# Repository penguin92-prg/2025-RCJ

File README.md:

# 2025-RCJ

## 👥Member

#### penguin92-prg [(bio)](https://github.com/penguin92-prg)
#### maguronoosushi0807 [(bio)](https://github.com/maguronoosushi0807)

## 🔗Links

- [penguin92-prg's blog](https://note.com/nearfactory)

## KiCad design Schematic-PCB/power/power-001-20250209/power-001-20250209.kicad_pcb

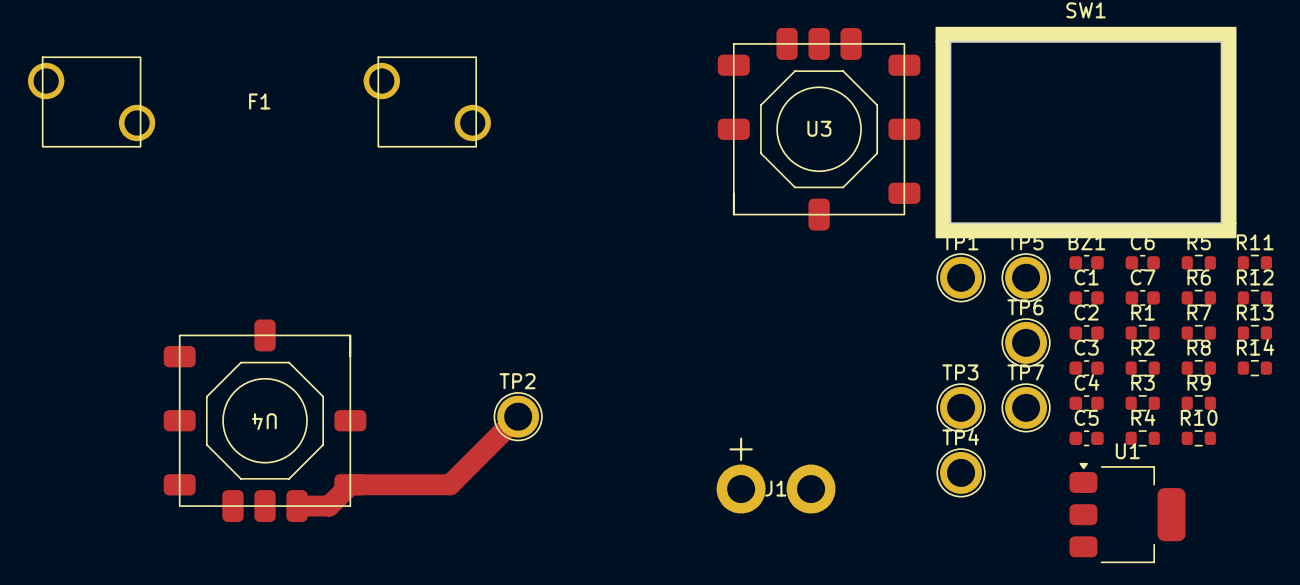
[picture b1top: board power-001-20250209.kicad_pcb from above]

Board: 2 copper layers, 35 parts (0 on the bottom side), 16 nets.

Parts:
BZ1: Buzzer; C_0603_1608Metric
C1, C2, C4, C6: 10uF; C_0603_1608Metric
C3: 0.1uF; C_0603_1608Metric
C5, C7: 22uF; C_0603_1608Metric
F1: 10A/15A; Fuse
J1: VIN
R1, R3, R5: 100K; R_0603_1608Metric
R2: 20K; R_0603_1608Metric
R4, R7, R11: 1K; R_0603_1608Metric
R6, R12: 330; R_0603_1608Metric
R8: 1.5K; R_0603_1608Metric
R9: 680; R_0603_1608Metric
R10: 1.2; R_0603_1608Metric
R13: 10; R_0603_1608Metric
R14: 1.2K; R_0603_1608Metric
SW1: Locker; RA1113112R
TP1, TP2, TP3, TP4, TP5, TP6, TP7: TestPoint; TestPoint_Plated_Hole_D2.0mm
U1: LM1117MP-3.3; SOT-223-3_TabPin2
U3, U4: OKL-T6-W12N-C

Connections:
+3.3V: C4.1, R10.1, TP4.1, U3.4 (VOUT), U3.5 (Sense)
+3.3VA: C2.1, C3.1, R7.1, U1.2 (VO)
+5V: C6.1, R14.1, TP3.1, U4.4 (VOUT), U4.5 (Sense)
+12V: C5.1, C7.1, TP2.1, U3.2 (VIN), U4.2 (VIN)
+BATT: C1.1, R1.1, R3.1, TP1.1, U1.3 (VI)
GND: BZ1.2 (-), C1.2, C2.2, C3.2, J1.2, R2.2, R5.2, TP5.1, TP6.1, U1.1 (GND)
ICSPDAT: R1.2, R2.1, TP7.1
unnamed: F1.1, J1.1
unnamed: R4.1, R5.1
unnamed: R8.2, R9.1
unnamed: R11.2, R12.1
unnamed: R12.2, R13.1
unnamed: C4.2, C5.2, R9.2, R10.2, U3.1 (ON/OFF), U3.3 (GND), U3.7 (GND)
unnamed: R8.1, U3.6 (Trim)
unnamed: C6.2, C7.2, R13.2, R14.2, U4.1 (ON/OFF), U4.3 (GND), U4.7 (GND)
unnamed: R11.1, U4.6 (Trim)

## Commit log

2025-02-08 add: 電源基板 ver.001 のプロジェクトを作成した
2025-02-09 update: 電源基板 ver.001 の回路図を完成させた
    DRが必要、ChatGPTを頼ってみる
2025-02-15 add: MD基板 ver.001 のプロジェクトを作成した
2025-03-04 add: ラインセンサ基板 ver.001 のプロジェクトを作成した
2025-03-04 add: LED/照度センサのデータシート/シンボルを追加した
2025-03-04 update: センサ部分を作った
2025-03-04 add: ATmega2560-16AUのシンボル/フットプリントを追加した
2025-03-04 add: キッカーのテストプログラムを追加した
2025-04-03 いろいろ追加した
2025-04-03 Update MD回路駆動部分完成
    信号入力部分・ロジック電源供給部分はまだ
2025-04-04 add: 実験用3Dプリントファイルを追加
2025-04-04 add: UI基板の回路図完成
    DRお願いしたい
2025-04-04 update: UI基板の保存場所修正
2025-04-05 update: UI基板の回路図のDRをした
2025-04-05 add: ラインセンサ基板の外形
    エンジェルリング部分の幅が狭かったら広げる
2025-04-05 add: キッカー基板の回路図仮完成
    DRお願いします
2025-04-05 add: ラインセンサ基板外形ver.002を追加
2025-04-05 update: キッカー基板の回路図をchatGPTのDRをもとに修正
2025-04-06 update: 電源基板の回路図を開いた
2025-04-07 add: モーターブラケットの3Dプリンタ印刷用ファイルを追加
2025-04-07 update: ファイル名・フォルダ名のリネーム
2025-04-13 update: メイン基板の回路図を作成した
2026-02-06 Summary (required)
